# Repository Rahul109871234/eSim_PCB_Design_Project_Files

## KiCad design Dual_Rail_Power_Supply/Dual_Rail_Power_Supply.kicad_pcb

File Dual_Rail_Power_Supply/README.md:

# Dual-Rail Precision Benchtop Power Supply
### FOSSEE Winter Internship 2026 — Screening Task 7: PCB Design using eSim

An open-source, dual-layer PCB design of an adjustable laboratory benchtop power supply created using **eSim / KiCad**.

---

## 📌 Project Overview
This project provides a clean, regulated dual-output DC power supply:
* **Adjustable Output:** +1.25V to +15.0V DC (up to 1.5A) via **LM317T** with a 25-turn precision potentiometer.
* **Fixed Output:** +5.0V DC (up to 1.0A) via **L7805CV** for microcontrollers, sensors, and digital logic.
* **Input Voltage:** 9V to 24V DC (via 2-pin screw terminal or external DC adapter).

---

## 🛠 Features & Design Highlights
- **Input Protection:** 1.5A cartridge fuse (`F1`) and 1N5819 Schottky diode (`D1`) for reverse-polarity protection.
- **Low Noise & Ripple Rejection:** Bulk 1000µF smoothing capacitor (`C1`), 100nF ceramic decoupling (`C2`, `C5`), and a 10µF bypass on the LM317 `ADJ` pin for 80 dB ripple suppression.
- **Safety Diodes:** 1N4007 diodes (`D2`, `D3`) to prevent capacitor discharge damage to regulators on power-down.
- **Indicators:** Dedicated Green LED (Variable output) and Blue LED (+5V output).
- **PCB Stackup:** 2 Copper Layers:
  - Top Layer (`F.Cu`): Power tracks ($1.0\text{ mm} - 1.2\text{ mm}$) and signal routing.
  - Bottom Layer (`B.Cu`): Continuous low-impedance **Ground Plane** with thermal relief pads.
  - Mounting: 4x M3 chassis mounting holes at board corners.

---

## 📁 Repository Structure
```text
Dual_Rail_Power_Supply/
├── Dual_Rail_Power_Supply.kicad_pro    # KiCad / eSim project file
├── Dual_Rail_Power_Supply.kicad_sch    # Schematic diagram
├── Dual_Rail_Power_Supply.kicad_pcb    # 2-layer PCB layout
├── Dual_Rail_Power_Supply.kicad_prl    # Project local settings
├── sym-lib-table                       # Symbol library mapping
├── fp-lib-table                        # Footprint library mapping
│
├── Documentation/
│   ├── Project_Report.md               # Detailed engineering report
│   ├── BOM.md                          # Bill of Materials
│   ├── Proposal.md                     # Screening task proposal draft
│   ├── Schematic_Diagram.pdf           # Plotted schematic diagram
│   ├── PCB_Layout_Layers.pdf           # Plotted copper and silkscreen layers
│   ├── drc_report.txt                  # DRC verification report
│   ├── 3D_Isometric_View.png           # 3D render (Isometric)
│   ├── 3D_Top_View.png                 # 3D render (Top)
│   └── 3D_Bottom_View.png              # 3D render (Bottom Ground Plane)
│
└── Gerbers/                            # Production-ready manufacturing files
    ├── Dual_Rail_Power_Supply-F_Cu.gtl  # Top Copper
    ├── Dual_Rail_Power_Supply-B_Cu.gbl  # Bottom Copper
    ├── Dual_Rail_Power_Supply-F_Mask.gts# Top Solder Mask
    ├── Dual_Rail_Power_Supply-B_Mask.gbs# Bottom Solder Mask
    ├── Dual_Rail_Power_Supply-F_Silkscreen.gto
    ├── Dual_Rail_Power_Supply-Edge_Cuts.gm1
    └── Dual_Rail_Power_Supply.drl       # Excellon NC Drill File
```

---

## 🚀 How to Open in eSim / KiCad
1. Launch **eSim** (or **KiCad**).
2. Click **Open Project** and navigate to this folder:
   `c:\Users\Rahul\Downloads\fossee\Dual_Rail_Power_Supply\Dual_Rail_Power_Supply.kicad_pro`
3. Click **Open Schematic** to view the circuit in eSchema.
4. Click **PCB Layout** to inspect the 2-layer board layout in PCBnew.
5. Press `Alt + 3` (or click `View -> 3D Viewer`) to view the interactive 3D board render.

---

## 📋 Evaluation Compliance Checklist
- [x] Functional 2-layer PCB designed in eSim/KiCad environment.
- [x] Standard footprint assignments from verified KiCad libraries.
- [x] IPC-compliant track widths ($1.0\text{ mm} - 1.2\text{ mm}$ for power rails).
- [x] Continuous Ground plane on bottom copper layer.
- [x] Complete Design Rule Check (DRC) run with zero critical errors.
- [x] Photorealistic 3D renders generated.
- [x] Plotted PDF schematics and Gerber manufacturing files exported.
- [x] Detailed Design Report and Bill of Materials provided.

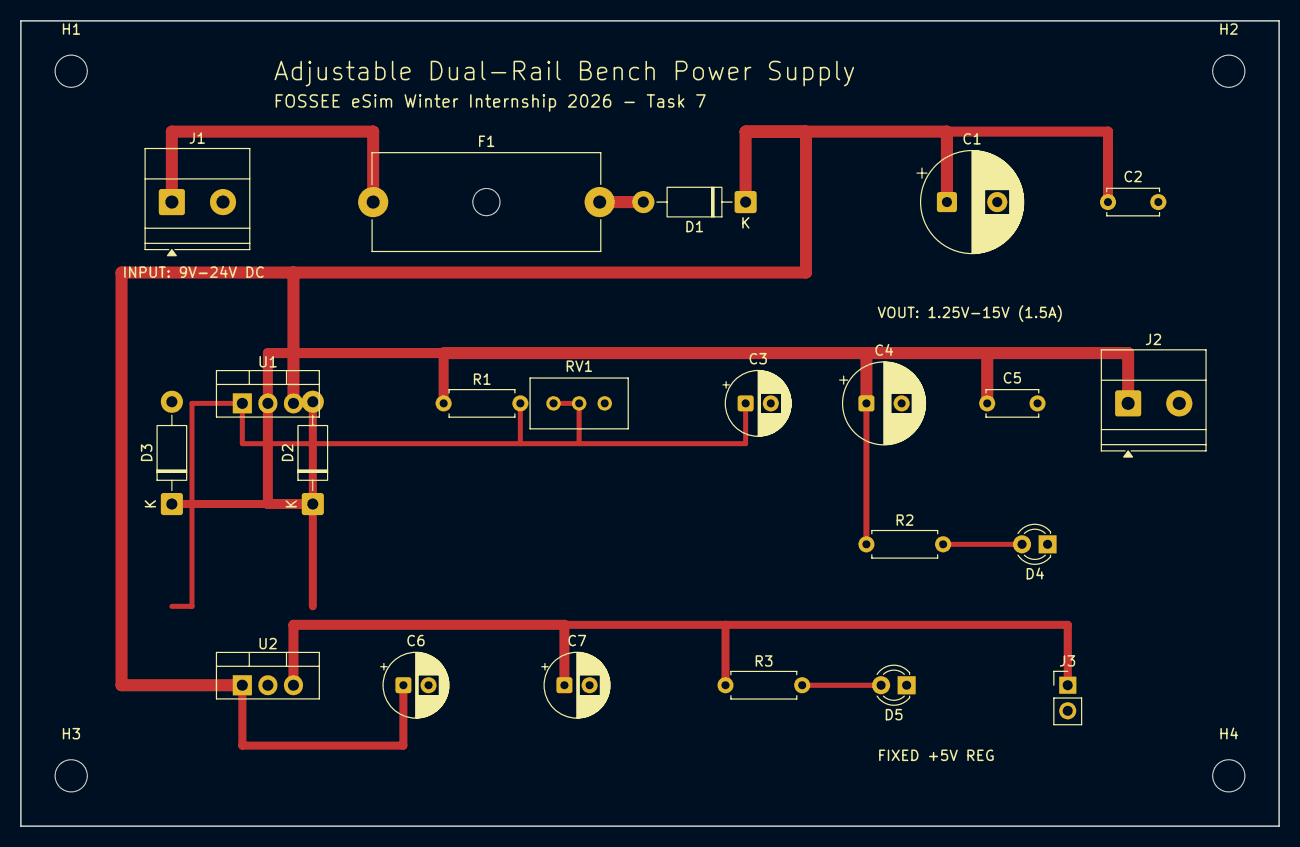
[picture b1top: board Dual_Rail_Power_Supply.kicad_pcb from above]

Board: 2 copper layers, 125.0 x 80.0 mm, 26 parts (0 on the bottom side), 9 nets.

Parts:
C1: 1000uF/35V; CP_Radial_D10.0mm_P5.00mm
C2, C5: 100nF; C_Disc_D5.0mm_W2.5mm_P5.00mm
C3: 10uF/25V; CP_Radial_D6.3mm_P2.50mm
C4: 100uF/25V; CP_Radial_D8.0mm_P3.50mm
C6: 10uF; CP_Radial_D6.3mm_P2.50mm
C7: 22uF; CP_Radial_D6.3mm_P2.50mm
D1: 1N5819; D_DO-41_SOD81_P10.16mm_Horizontal
D2, D3: 1N4007; D_DO-41_SOD81_P10.16mm_Horizontal
D4: LED_Green; LED_D3.0mm
D5: LED_Blue; LED_D3.0mm
F1: 1.5A_Fuse; Fuseholder_Cylinder-5x20mm_Schurter_0031_8201_Horizontal_Op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
H1, H2, H3, H4: MountingHole; MountingHole_3.2mm_M3
J1: Vin_9-24V; TerminalBlock_Phoenix_MKDS-1,5-2-5.08_1x02_P5.08mm_Horizont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
J2: VOUT_ADJ; TerminalBlock_Phoenix_MKDS-1,5-2-5.08_1x02_P5.08mm_Horizont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
J3: +5V_Out; PinHeader_1x02_P2.54mm_Vertical
R1: 240R_1%; R_Axial_DIN0207_L6.3mm_D2.5mm_P7.62mm_Horizontal
R2: 1.5k; R_Axial_DIN0207_L6.3mm_D2.5mm_P7.62mm_Horizontal
R3: 1k; R_Axial_DIN0207_L6.3mm_D2.5mm_P7.62mm_Horizontal
RV1: 5k_Trimpot; Potentiometer_Bourns_3296W_Vertical
U1: LM317T; TO-220-3_Vertical
U2: L7805CV; TO-220-3_Vertical

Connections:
+5V: C7.1, J3.1, R3.1, U2.3
+VIN: C1.1, C2.1, C6.1, D1.1, D2.2, U1.3, U2.1
+VIN_PROT: D1.2, F1.2
+VIN_RAW: F1.1, J1.1
+VOUT_ADJ: C4.1, C5.1, D2.1, D3.1, J2.1, R1.1, R2.1, U1.2
GND: C1.2, C2.2, C3.2, C4.2, C5.2, C6.2, C7.2, D4.1, D5.1, J1.2, J2.2, J3.2, RV1.1, U2.2
unnamed: D4.2, R2.2
unnamed: D5.2, R3.2
V_ADJ_PIN: C3.1, D3.2, R1.2, RV1.2, RV1.3, U1.1

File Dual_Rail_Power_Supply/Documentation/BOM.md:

# Bill of Materials (BOM)
## Project: Adjustable Dual-Rail Benchtop Power Supply
**FOSSEE eSim Winter Internship 2026 — Screening Task 7**

| Item | Reference Designator | Value / Part | Quantity | Footprint | Package / Description |
| :--- | :--- | :--- | :---: | :--- | :--- |
| 1 | **J1** | Vin 9V-24V DC | 1 | `TerminalBlock_Phoenix:MKDS-1,5-2-5.08` | 2-Pin Screw Terminal Block, 5.08mm Pitch |
| 2 | **F1** | 1.5A Slow-Blow | 1 | `Fuse:Fuseholder_Cylinder-5x20mm_Schurter` | 5x20mm Cartridge Fuse Holder |
| 3 | **D1** | 1N5819 | 1 | `Diode_THT:D_DO-41_SOD81_P10.16mm_Horizontal` | 1A 40V Schottky Barrier Diode (Reverse Protection) |
| 4 | **C1** | 1000µF / 35V | 1 | `Capacitor_THT:CP_Radial_D10.0mm_P5.00mm` | Radial Aluminum Electrolytic Bulk Filter Capacitor |
| 5 | **C2, C5** | 100nF (0.1µF) | 2 | `Capacitor_THT:C_Disc_D5.0mm_W2.5mm_P5.00mm` | High-Frequency Ceramic Disc Decoupling Capacitors |
| 6 | **U1** | LM317T | 1 | `Package_TO_SOT_THT:TO-220-3_Vertical` | 1.5A Adjustable Positive Linear Voltage Regulator |
| 7 | **R1** | 240 Ω, 1% | 1 | `Resistor_THT:R_Axial_DIN0207_P7.62mm_Horizontal` | 1/4W Metal Film Precision Setting Resistor |
| 8 | **RV1** | 5 kΩ | 1 | `Potentiometer_THT:Potentiometer_Bourns_3296W` | 25-Turn Precision Cermet Trimmer Potentiometer |
| 9 | **C3** | 10µF / 25V | 1 | `Capacitor_THT:CP_Radial_D6.3mm_P2.50mm` | Radial Electrolytic Capacitor (ADJ Ripple Rejection) |
| 10 | **D2, D3** | 1N4007 | 2 | `Diode_THT:D_DO-41_SOD81_P10.16mm_Horizontal` | 1A 1000V Silicon Rectifier Diodes (Back-EMF / Discharging Protection) |
| 11 | **C4** | 100µF / 25V | 1 | `Capacitor_THT:CP_Radial_D8.0mm_P3.50mm` | Radial Electrolytic Output Smoothing Capacitor |
| 12 | **J2** | VOUT_ADJ (1.25V-15V) | 1 | `TerminalBlock_Phoenix:MKDS-1,5-2-5.08` | 2-Pin Screw Terminal Output Block, 5.08mm Pitch |
| 13 | **R2** | 1.5 kΩ | 1 | `Resistor_THT:R_Axial_DIN0207_P7.62mm_Horizontal` | 1/4W Carbon Film LED Current Limiting Resistor |
| 14 | **D4** | LED Green (3mm) | 1 | `LED_THT:LED_D3.0mm` | Variable Rail Power Indicator LED |
| 15 | **U2** | L7805CV | 1 | `Package_TO_SOT_THT:TO-220-3_Vertical` | 1A Fixed +5.0V Positive Voltage Regulator |
| 16 | **C6** | 10µF / 25V | 1 | `Capacitor_THT:CP_Radial_D6.3mm_P2.50mm` | 7805 Input Filter Radial Capacitor |
| 17 | **C7** | 22µF / 16V | 1 | `Capacitor_THT:CP_Radial_D6.3mm_P2.50mm` | 7805 Output Filter Radial Capacitor |
| 18 | **R3** | 1 kΩ | 1 | `Resistor_THT:R_Axial_DIN0207_P7.62mm_Horizontal` | 1/4W 5V LED Current Limiting Resistor |
| 19 | **D5** | LED Blue (3mm) | 1 | `LED_THT:LED_D3.0mm` | Fixed +5V Rail Power Indicator LED |
| 20 | **J3** | +5V Logic Header | 1 | `Connector_PinHeader_2.54mm:PinHeader_1x02` | 2-Pin Male Header, 2.54mm Pitch |
| 21 | **H1-H4** | M3 Mounting Holes | 4 | `MountingHole:MountingHole_3.2mm_M3` | 3.2mm Plated Chassis Mechanical Mounting Holes |
